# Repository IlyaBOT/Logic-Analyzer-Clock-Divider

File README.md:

# ACT161 Frequency Divider - R4

Основная редактируемая ревизия R4, KiCad 10.0.6, обновлена 2026-10-09. Прежняя папка R3 удалена. Взята ваша ручная разводка R4: все её дорожки/via, положения компонентов и контур сохранены. Текущий размер платы 42.8x27.6x1.6mm; два слоя, DIP-16/SCS-16 и четыре отверстия M3.

**До изготовления: оба торцевых разъёма UNVERIFIED, реальная распиновка/уровни анализатора неизвестны. Аппаратных измерений на 80MHz нет.**

Открыть `ACT161_Frequency_Divider.kicad_pro` в KiCad 10 или совместимой новой версии. Переносить всю папку: символы, footprint и модели локальные, пути `${KIPRJMOD}`. Схема и PCB нативные; генераторы не нужны для ручного редактирования.

## Изменения R4

J2 расположен на левой кромке, J3 - на правой. У каждого пять SMD-площадок F.Cu и пять B.Cu, без отверстий и без пасты. J3 больше не является нижним THT-разъёмом. Нечётные контакты обоих разъёмов на F.Cu, чётные на B.Cu; строки 1/2 сверху. Механические модели этих разъёмов отсутствуют: выполнена 2D-проверка, посадка реальных деталей не подтверждена.

SN74LVC125APW, C3 и выходные селекторные резисторы удалены. R1-R4=47R соединяют QA/QB/QC/QD напрямую с DIV2/4/8/16. По умолчанию U1 CD74ACT161E получает 5V через R5=0R; R6, U3, C4 не устанавливаются. LED питается от общей входной шины 5V (USB или J4). Пять PASS проходят напрямую между одинаковыми номерами J2/J3. USB +5V не соединено с контактами J2/J3.

## Питание проводами через J4

Между Micro-USB J1 и LED1 установлена вертикальная штыревая гребёнка J4 1x2, шаг 2.54mm, отверстия 1mm. При виде сверху, USB наверху: верхний квадратный контакт 1 = +5V, нижний круглый контакт 2 = GND. Полярность подписана на плате. Гребёнка включена в BOM и в схему, footprint и STEP локальные.

Подать стабилизированные 5V и общий GND от основной схемы. USB и J4 соединены с одной шиной напрямую: использовать только один источник за раз. При питании через J4 отключить USB-кабель, иначе питание может попасть в USB-порт. В опциональной сборке с выходами 3.3V на J4 по-прежнему подаются 5V; это вход до U3. LED работает от любого из этих двух входов.

В исходной R4 дополнены пять незавершённых соединений у J2/J3, исправлены пересечения/размер надписей и расстояние между QR и ссылкой. Исходные нативные файлы сохранены в `reports/user_R4_original.zip`; сравнение геометрии - `input_user_layout.json` и тест сохранения пользовательской разводки.

## Опция 3.3V без выходного буфера

Это отдельный вариант сборки с заменой U1, а не переключение напряжения установленного ACT161. При выключенном питании удалить R5, заменить CD74ACT161E в панельке на совместимый по выводам CD74AC161E, установить U3 TLV75533PDBVR, C4 и R6=0R. Все управляющие входы и развязка U1 питаются от выбранного VCC_LOGIC. Одновременно R5/R6 не устанавливать: это соединит 5V с выходом 3.3V стабилизатора.

CD74ACT161E требует 4.5-5.5V и не допускается в сборке 3.3V. Для CD74AC161E при 3.3V datasheet гарантирует до 64MHz (-55..125C), 73MHz (-40..85C), а не 80MHz. CLK должен быть 0..VCC и с полными CMOS-уровнями; 5V CLK напрямую запрещён в режиме 3.3V. Если 3.3V выходы нужны при 80MHz с сохранением ACT161, потребуется внешний преобразователь уровней либо отдельная переработка схемы. Источники и временные параметры в `reports/validation.md`.

## Проверки и файлы

Сохранённые ERC/DRC, 15 успешных тестов и `final_audit.txt` в `reports/` относятся к снимку из `checked_sha256.json`. Текущие PCB и `.kicad_pro` отличаются от этого снимка. Повторная проверка 2026-10-17: ERC без нарушений; DRC без ошибок, с одним предупреждением о несовпадении J4 с библиотечным footprint; тесты 13/15, два расхождения с прежней компоновкой. Подробности и список файлов для очистки — `reports/repository_audit.md`. Прежняя проверка переноса выполнялась в другой папке на этом же ПК, не на другой машине.

`docs/` содержит PDF схемы, двух copper и двух assembly видов, а также `pinout.md`. `previews/` содержит PNG, SVG каждого слоя и два настоящих 3D-рендера KiCad. BOM и варианты сборки в `reports/BOM.csv` и `assembly_variants.json`.

Чертежи и изображения относятся к исходникам, записанным в `reports/export_manifest.json`; после изменений PCB их нужно обновить. `.gitignore` исключает автокопии и локальные настройки KiCad, файлы Freerouting, кэши Python, старые генераторы и их логи. Нативные файлы, локальные библиотеки, документация, актуальные отчёты и `reports/user_R4_original.zip` остаются доступными для Git.

`scripts/check_native.py` запускает ERC/DRC/tests в этой установке KiCad. Старые генераторы `design.py` и `build_pcb.py` заблокированы от запуска, чтобы не перезаписать вашу ручную разводку. Нативные KiCad-файлы - основной источник проекта. `export.py` обновляет чертежи, `document.py` документацию. В скриптах заданы пути к установленным здесь KiCad/Poppler.

Перед подключением проверить pinout и допустимые уровни анализатора, посадку обоих торцевых разъёмов, точную панельку и приобретённые MLCC/LED. Подавать CLK после стабилизации питания; измерять питание и CLK у U1.2, начинать с низкой частоты. Выходы рассчитаны на высокоомные входы, не на DC-нагрузку 50ohm. В фазе включения счётчика нет определённого сброса. Прямой счёт 433MHz не предусмотрен. Gerber/Drill не выпускались, изготовление не заказывалось.

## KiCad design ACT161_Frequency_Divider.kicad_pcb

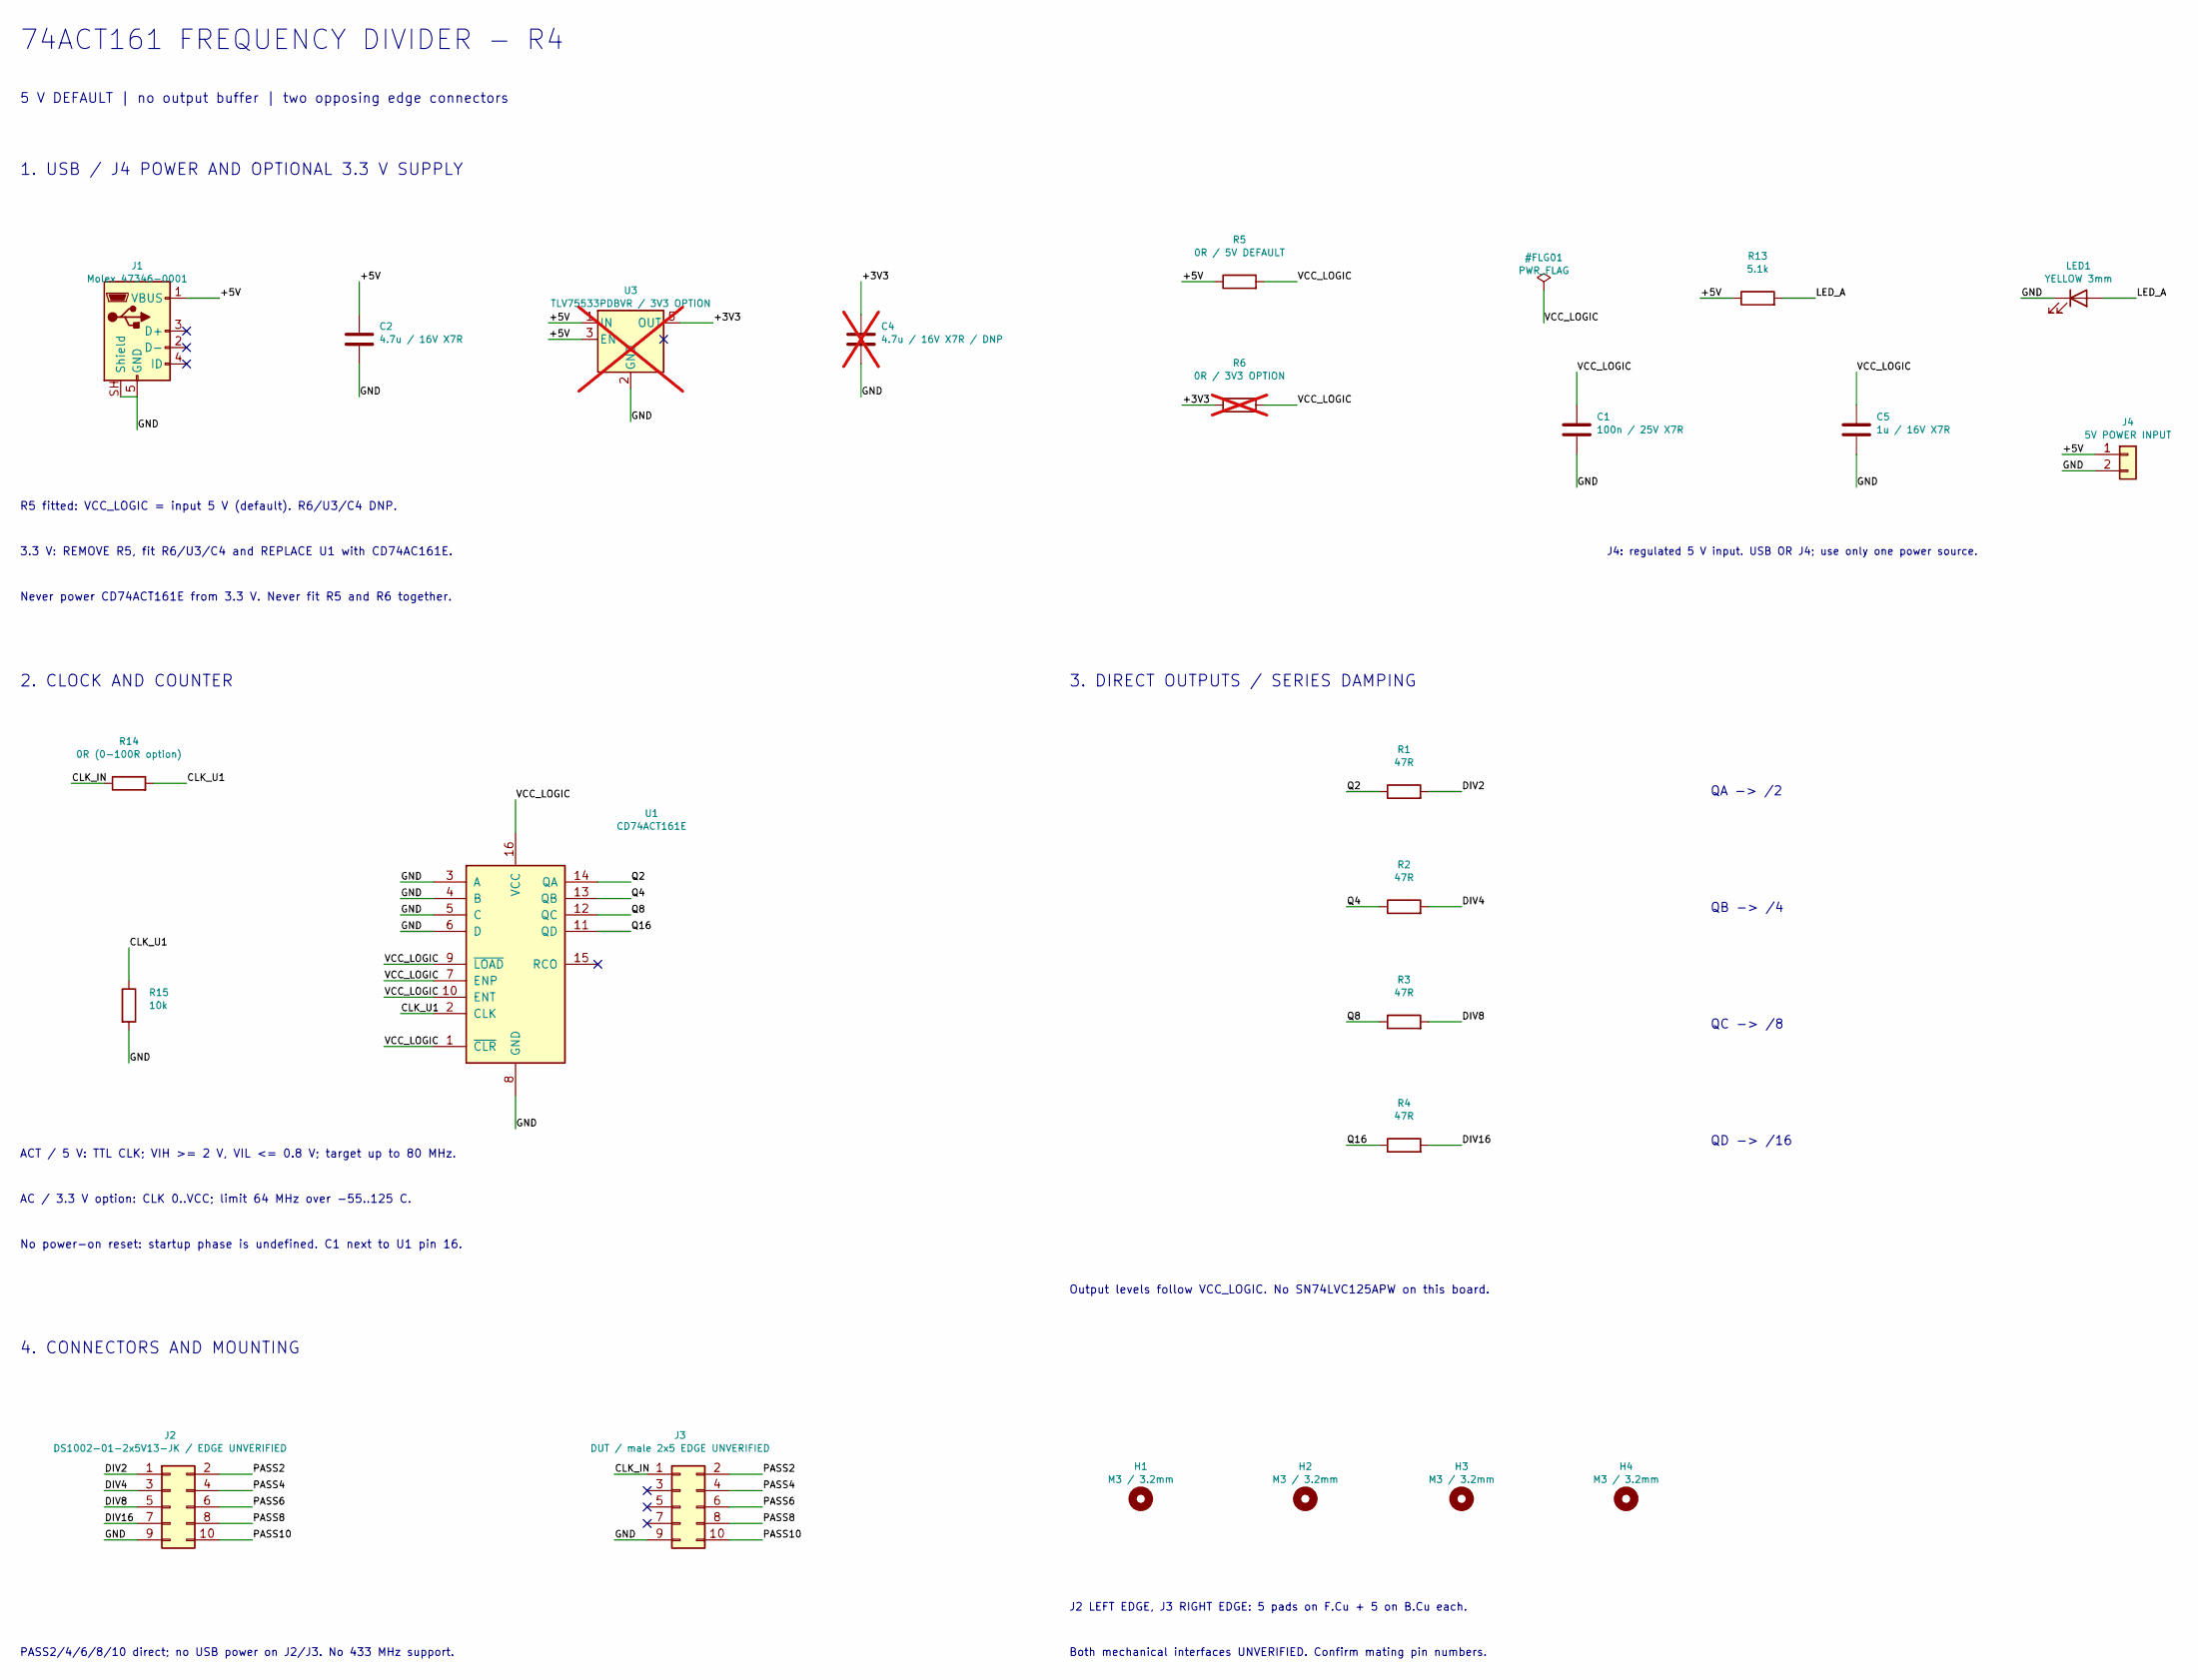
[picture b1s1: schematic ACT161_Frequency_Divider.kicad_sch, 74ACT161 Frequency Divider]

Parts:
C1: 100n / 25V X7R; C_0603_1608Metric
C2: 4.7u / 16V X7R; C_0805_2012Metric
C4: 4.7u / 16V X7R / DNP; C_0805_2012Metric; not fitted
C5: 1u / 16V X7R; C_0805_2012Metric
H1, H2, H3, H4: M3 / 3.2mm; MountingHole_3.2mm_M3
J1: Molex 47346-0001; USB_Micro-B_Molex_47346-0001
J2: DS1002-01-2x5V13-JK / EDGE UNVERIFIED; J2_Edge_2x05
J3: DUT / male 2x5 EDGE UNVERIFIED; J3_Edge_2x05
J4: 5V POWER INPUT; PinHeader_1x02_P2.54mm_Vertical
LED1: YELLOW 3mm; LED_D3.0mm
R1, R2, R3, R4: 47R; R_0603_1608Metric
R5: 0R / 5V DEFAULT; R_0603_1608Metric
R6: 0R / 3V3 OPTION; R_0603_1608Metric; not fitted
R13: 5.1k; R_0603_1608Metric
R14: 0R (0-100R option); R_0603_1608Metric
R15: 10k; R_0603_1608Metric
U1: CD74ACT161E; DIP-16_W7.62mm_Socket
U3: TLV75533PDBVR / 3V3 OPTION; SOT-23-5; not fitted

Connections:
/+3V3: C4.1, R6.1, U3.5 (OUT)
/+5V: C2.1, J1.1 (VBUS), J4.1, R5.1, R13.1, U3.1 (IN), U3.3 (EN)
/CLK_IN: J3.1, R14.1
/CLK_U1: R14.2, R15.1, U1.2 (CLK)
/DIV2: J2.1, R1.2
/DIV4: J2.3, R2.2
/DIV8: J2.5, R3.2
/DIV16: J2.7, R4.2
/GND: C1.2, C2.2, C4.2, C5.2, J1.5 (GND), J1.SH (Shield), J2.9, J3.9, J4.2, LED1.1 (K), R15.2, U1.3 (A), U1.4 (B), U1.5 (C), U1.6 (D), U1.8 (GND), U3.2 (GND)
/LED_A: LED1.2 (A), R13.2
/PASS2: J2.2, J3.2
/PASS4: J2.4, J3.4
/PASS6: J2.6, J3.6
/PASS8: J2.8, J3.8
/PASS10: J2.10, J3.10
/Q2: R1.1, U1.14 (QA)
/Q4: R2.1, U1.13 (QB)
/Q8: R3.1, U1.12 (QC)
/Q16: R4.1, U1.11 (QD)
/VCC_LOGIC: C1.1, C5.1, R5.2, R6.2, U1.1 (~CLR), U1.7 (ENP), U1.9 (~LOAD), U1.10 (ENT), U1.16 (VCC)

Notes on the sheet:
74ACT161 FREQUENCY DIVIDER - R4
5 V DEFAULT | no output buffer | two opposing edge connectors
1. USB / J4 POWER AND OPTIONAL 3.3 V SUPPLY
R5 fitted: VCC_LOGIC = input 5 V (default). R6/U3/C4 DNP.
3.3 V: REMOVE R5, fit R6/U3/C4 and REPLACE U1 with CD74AC161E.
Never power CD74ACT161E from 3.3 V. Never fit R5 and R6 together.
2. CLOCK AND COUNTER
ACT / 5 V: TTL CLK; VIH >= 2 V, VIL <= 0.8 V; target up to 80 MHz.
AC / 3.3 V option: CLK 0..VCC; limit 64 MHz over -55..125 C.
No power-on reset: startup phase is undefined. C1 next to U1 pin 16.
3. DIRECT OUTPUTS / SERIES DAMPING
QA -> /2
QB -> /4
QC -> /8
QD -> /16
Output levels follow VCC_LOGIC. No SN74LVC125APW on this board.
4. CONNECTORS AND MOUNTING
J2 LEFT EDGE, J3 RIGHT EDGE: 5 pads on F.Cu + 5 on B.Cu each.
Both mechanical interfaces UNVERIFIED. Confirm mating pin numbers.
PASS2/4/6/8/10 direct; no USB power on J2/J3. No 433 MHz support.
J4: regulated 5 V input. USB OR J4; use only one power source.

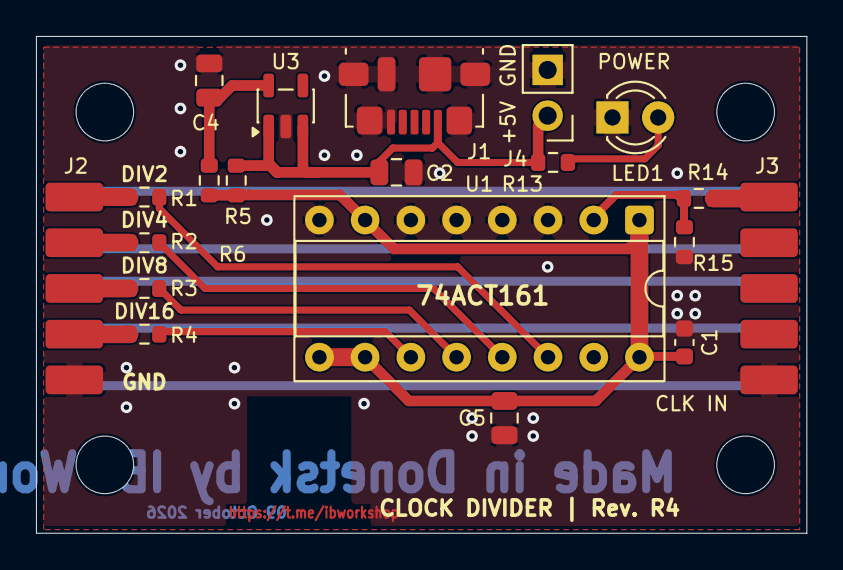
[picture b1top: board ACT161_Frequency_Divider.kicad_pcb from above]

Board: 2 copper layers, 42.8 x 27.6 mm, 24 parts (0 on the bottom side), 20 nets.
